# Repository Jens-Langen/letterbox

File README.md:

# letterbox
Smarter Briefkasten

Details: http://www.langen.koeln/wp/?p=11

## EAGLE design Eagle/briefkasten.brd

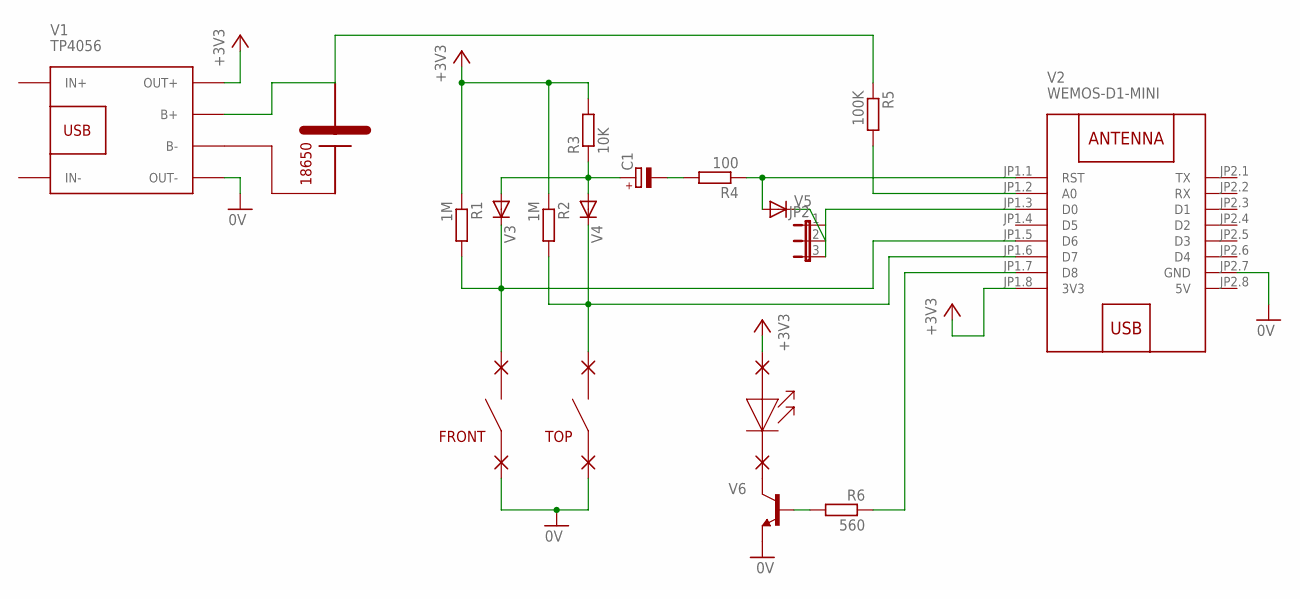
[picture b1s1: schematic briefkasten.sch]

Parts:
C1: CPOL-EUE2.5-5; E2,5-5
JP2: JP2E; JP2
PAD7, PAD8, PAD9, PAD10, PAD11, PAD12: 1,6/0,9
R1, R2: 1M; 0207/7
R3: 10K; 0207/7
R4: 100; 0309V
R5: 100K; 0207/7
R6: 560; 0207/7
V1: TP4056; BATTERY-CHARGER-LI-PROT
V2: WEMOS-D1-MINI
V3, V4: 1N4148DO35-7; DO35-7
V5: DIODE-D-2.5; D-2.5
V6: -NPN-TO92-EBC; TO92-EBC

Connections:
0V: PAD10.1, PAD12.1, V1.OUT-, V2.JP2.7 (GND), V6.E
5V: V2.JP2.8 (5V)
+3V3: PAD8.1, R1.1, R2.1, R3.2, V1.OUT+, V2.JP1.8 (3V3)
unnamed: PAD7.1, V6.C
unnamed: PAD11.1, R2.2, V2.JP1.6 (D7), V4.C
unnamed: C1.-, R4.2
unnamed: JP2.2, V5.C
unnamed: R4.1, V2.JP1.1 (RST), V5.A
unnamed: C1.+, R3.1, V3.A, V4.A
unnamed: R5.1, V1.B+
unnamed: PAD9.1, R1.2, V2.JP1.5 (D6), V3.C
unnamed: R5.2, V2.JP1.2 (A0)
unnamed: JP2.3, V2.JP1.3 (D0)
unnamed: R6.1, V2.JP1.7 (D8)
unnamed: R6.2, V6.B

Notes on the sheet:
18650
TOP
FRONT

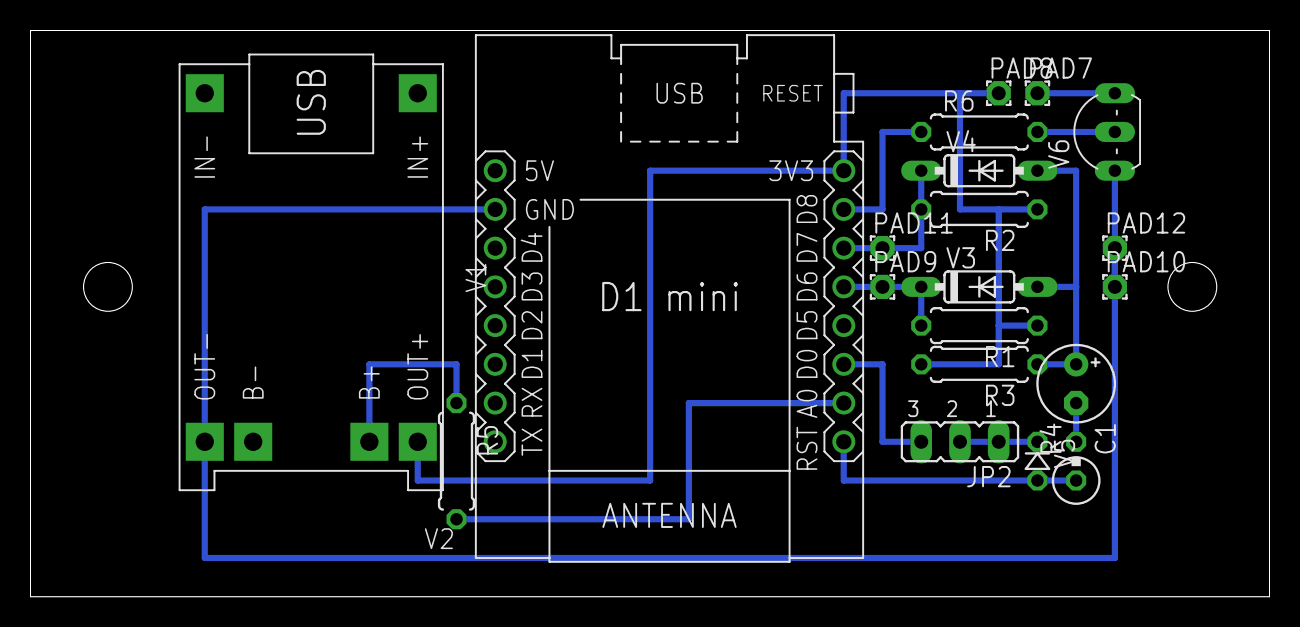
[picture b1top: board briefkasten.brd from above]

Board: 2 copper layers, 81.3 x 37.1 mm, 20 parts (0 on the bottom side), 14 nets.

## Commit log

2019-02-04 Initial
2019-02-04 move settings in seperate file
2019-02-05 fast opening send fail state
2020-05-20 Only the top button was send

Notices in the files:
parts and their libraries:
diy-modules: Released under the Creative Commons Attribution 4.0 International License: http://creativecommons.org/licenses/by/4.0
